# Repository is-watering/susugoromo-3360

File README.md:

# PMW3360 Breakout Board - SUSUGOROMO-3360（煤衣-3360）

## 寸法図/Dimensions

## 回路図/Schematic
* [PDF](img/schematic.pdf)

## ピン番号
|1  |2   |3   |4   |5     |6  |7  |
|---|----|----|----|------|---|---|
|NCS|MISO|MOSI|SCLK|MOTION|3V3|GND|

## 部品表/BOM

| Reference      | Value               | Footprint | Qty |
| -------------- | ------------------- | --------- | --- |
| C1, C4         | 0.1uF               | 0805      | 2   |
| C2             | 1uF                 | 0805      | 1   |
| C3             | 4.7uF/10V           | 0805      | 1   |
| R2, R3         | 10k                 | 0805      | 2   |
| R1             | 39R                 | 0805      | 1   |
| U1             | TLV70019DDCR        | SOT23-5   | 1   |
| U2             | PMW3360DM-T2QU      |           | 1   |

## Dependencies (KiCad)
* [is-watering/isw-kbd-lib](https://github.com/is-watering/isw-kbd-lib)

## ライセンス/License
This project is licensed under the CERN OHL-P v2.
You may use, distribute, and modify this design under the terms of the CERN OHL-P v2.
Original design by snize.

### 本プロジェクトを利用する場合について
- 著作権表示とライセンスの表示を残してください

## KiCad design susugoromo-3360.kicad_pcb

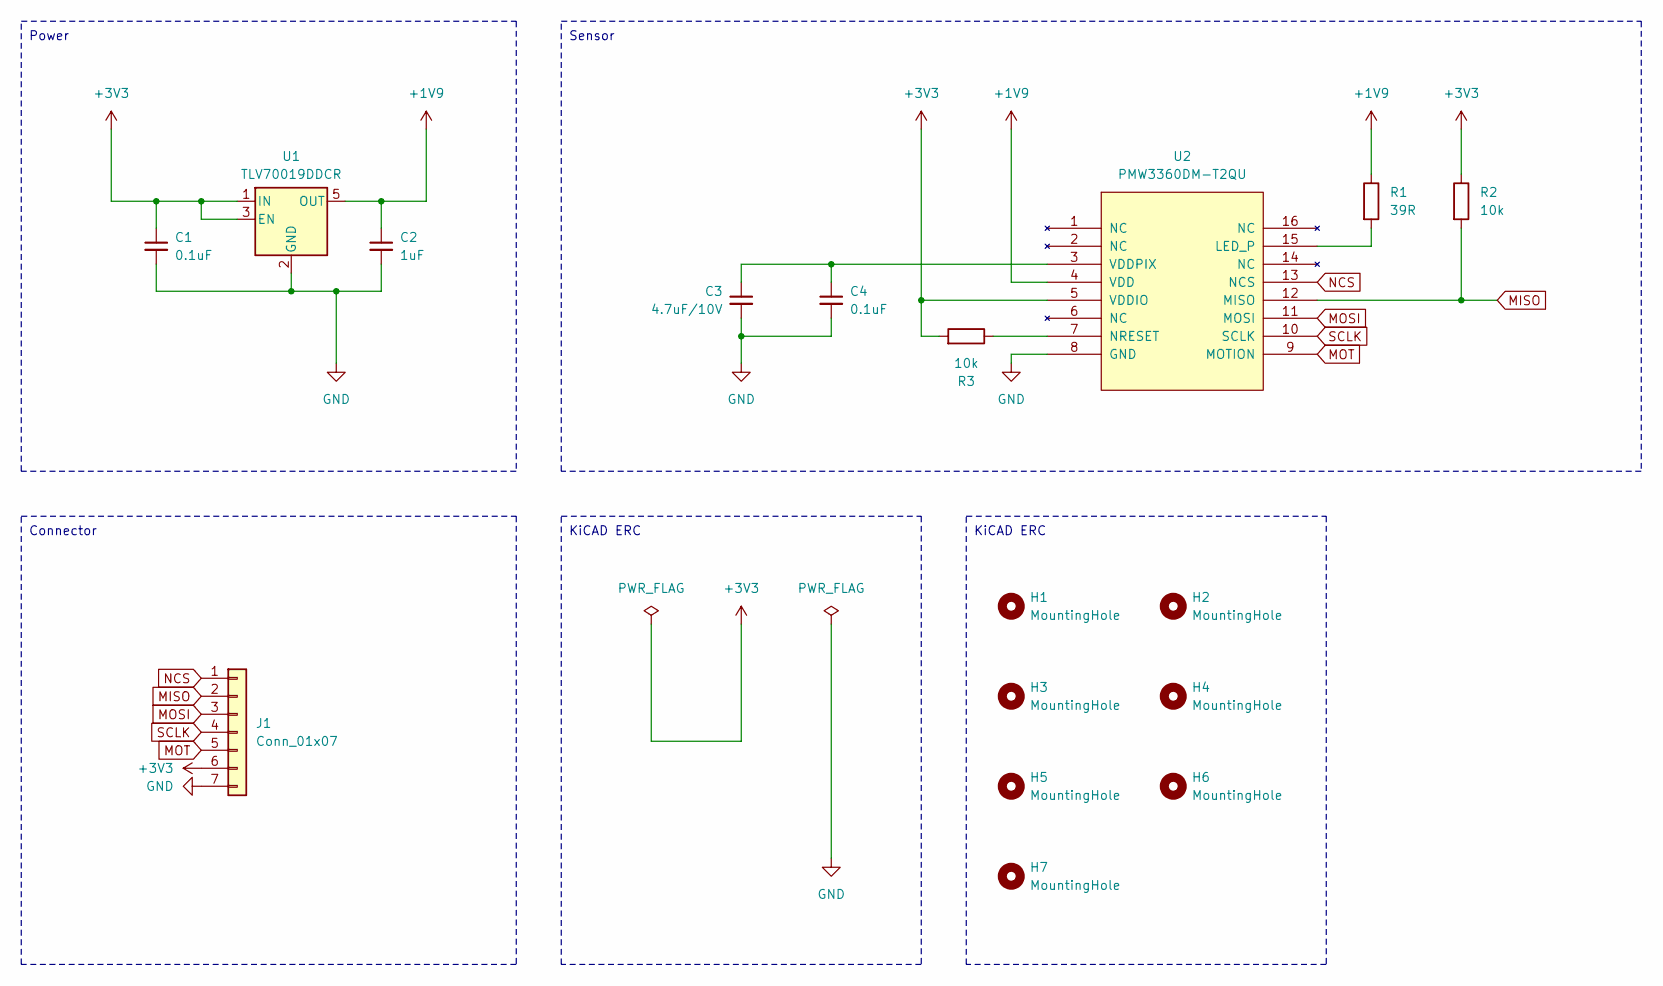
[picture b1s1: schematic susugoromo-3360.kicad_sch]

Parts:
C1, C4: 0.1uF; C_0805_2012Metric_Pad1.18x1.45mm_HandSolder
C2: 1uF; C_0805_2012Metric_Pad1.18x1.45mm_HandSolder
C3: 4.7uF/10V; C_0805_2012Metric_Pad1.18x1.45mm_HandSolder
H1, H2, H3, H4, H5, H6, H7: MountingHole; M2_ScrewHole_EdgeCuts
J1: Conn_01x07; PinHeader_1x07_P2.54mm_Horizontal
R1: 39R; R_0805_2012Metric_Pad1.20x1.40mm_HandSolder
R2, R3: 10k; R_0805_2012Metric_Pad1.20x1.40mm_HandSolder
U1: TLV70019DDCR; SOT-23-5_HandSoldering
U2: PMW3360DM-T2QU

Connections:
+1V9: C2.1, R1.1, U1.5 (OUT), U2.4 (VDD)
+3V3: C1.1, J1.6, R2.1, R3.2, U1.1 (IN), U1.3 (EN), U2.5 (VDDIO)
GND: C1.2, C2.2, C3.2, C4.2, J1.7, U1.2 (GND), U2.8 (GND)
MISO: J1.2, R2.2, U2.12 (MISO)
MOSI: J1.3, U2.11 (MOSI)
MOT: J1.5, U2.9 (MOTION)
NCS: J1.1, U2.13 (NCS)
unnamed: R1.2, U2.15 (LED_P)
unnamed: R3.1, U2.7 (NRESET)
unnamed: C3.1, C4.1, U2.3 (VDDPIX)
SCLK: J1.4, U2.10 (SCLK)

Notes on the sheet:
Power
Sensor
KiCAD ERC
Connector

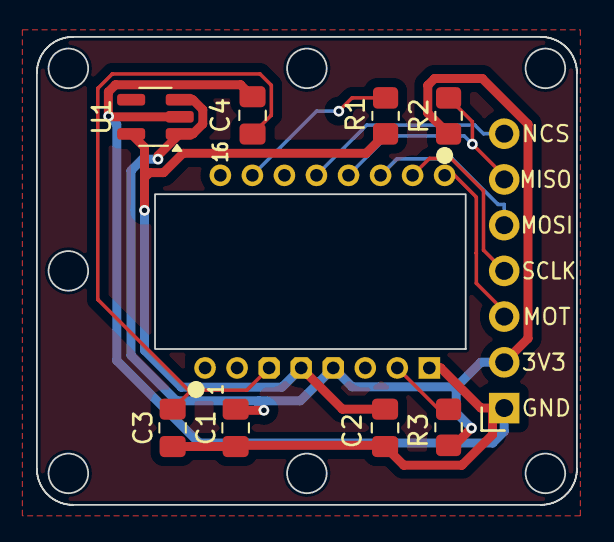
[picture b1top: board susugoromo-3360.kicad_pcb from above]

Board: 2 copper layers, 30.0 x 26.0 mm, 17 parts (0 on the bottom side), 11 nets.

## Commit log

2025-05-21 update: readme, add: kicad-files
2025-05-21 update: gitignore

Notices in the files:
susugoromo-3360.kicad_pcb:
© 2025 is-watering
